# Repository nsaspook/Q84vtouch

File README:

Turbopump RS485 DCU readout emulator

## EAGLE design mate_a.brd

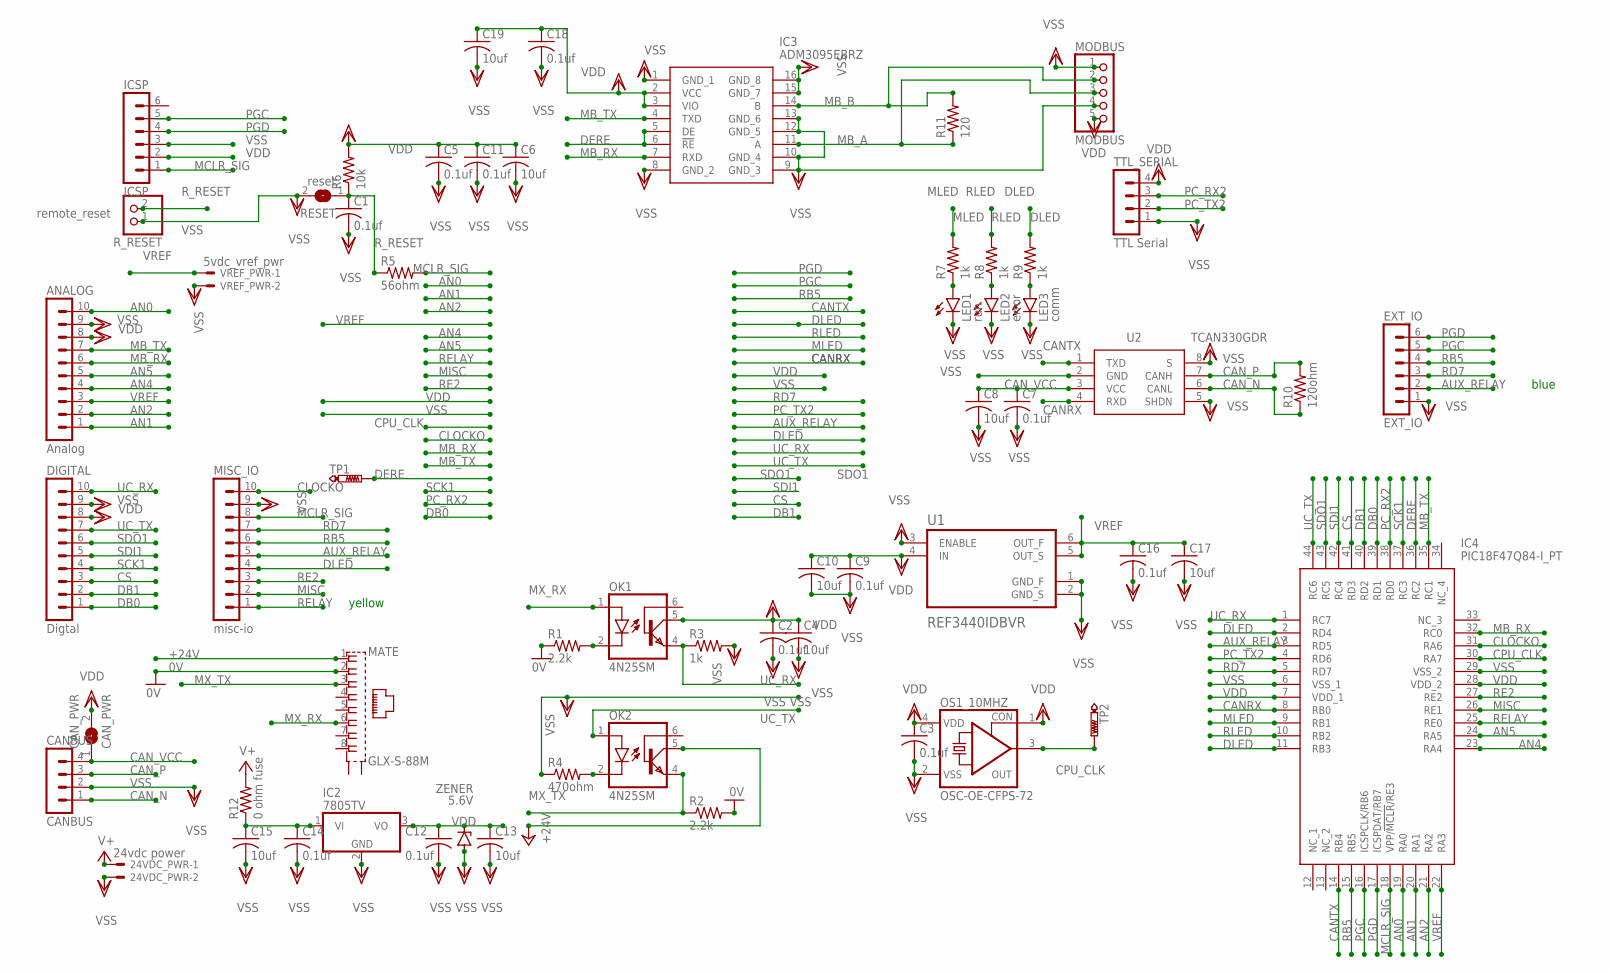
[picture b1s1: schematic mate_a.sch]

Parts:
24VDC_PWR: 24vdc power; 22-23-2021
ANALOG: Analog; MA10-1
C1, C2, C3, C5, C7, C9, C11, C12, C14, C16, C18: 0.1uf; C0805
C4, C6, C8, C10, C13, C15, C17, C19: 10uf; C0805
CANBUS: CANBUS; MA04-1
CAN_PWR: CAN_PWR; SJ
DIGITAL: Digtal; MA10-1
EXT_IO: EXT_IO; MA06-1
IC2: 7805TV; TO220V
IC3: ADM3095EBRZ; SOIC127P600X175-16N
IC4: PIC18F47Q84-I_PT; QFP80P1200X1200X120-44N
ICSP: ICSP; MA06-1
LED1: run; CHIPLED_0805
LED2: error; CHIPLED_0805
LED3: comm; CHIPLED_0805
MATE: GLX-S-88M
MISC_IO: misc-io; MA10-1
MODBUS: MODBUS; 1X05
OK1, OK2: 4N25SM; DIL6-SMD
OS1_10MHZ: OSC-OE-CFPS-72; 7.2X5.2-4-PAD
R1, R2: 2.2k; R0805
R3, R7, R8, R9: 1k; R0805
R4: 470ohm; R0805
R5: 56ohm; R0805
R6: 10k; R0805
R10: 120ohm; R0805
R11: 120; R0805
R12: 0 ohm fuse; R1206
RESET: reset; SJ
R_RESET: remote_reset; 1X02
TP1, TP2: PTR1PAD1-13; P1-13
TTL_SERIAL: TTL Serial; MA04-1
U1: REF3440IDBVR; SOT95P280X145-6N
U2: TCAN330GDR; SOIC127P600X175-8N
VREF_PWR: 5vdc_vref_pwr; 22-23-2021
ZENER: 5.6V; SMB

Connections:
0V: MATE.2, R1.1, R2.2
+24V: MATE.1, OK2.5 (COL)
AN0: ANALOG.10, IC4.19 (RA0)
AN1: ANALOG.1, IC4.20 (RA1)
AN2: ANALOG.2, IC4.21 (RA2)
AN4: ANALOG.4, IC4.23 (RA4)
AN5: ANALOG.5, IC4.24 (RA5)
AUX_RELAY: EXT_IO.2, IC4.3 (RD5), MISC_IO.5
CANRX: IC4.8 (RB0), U2.4 (RXD)
CANTX: IC4.14 (RB4), U2.1 (TXD)
CAN_N: CANBUS.1, R10.1, U2.6 (CANL)
CAN_P: CANBUS.3, R10.2, U2.7 (CANH)
CAN_VCC: C7.1, C8.1, CANBUS.4, CAN_PWR.1, U2.3 (VCC)
CLOCKO: IC4.31 (RA6), MISC_IO.10
CPU_CLK: IC4.30 (RA7), OS1_10MHZ.3 (OUT), TP2.TP
CS: DIGITAL.3, IC4.41 (RD3)
DB0: DIGITAL.1, IC4.39 (RD1)
DB1: DIGITAL.2, IC4.40 (RD2)
DERE: IC3.5 (DE), IC3.6 (!RE), IC4.36 (RC2), TP1.TP
DLED: IC4.2 (RD4), IC4.11 (RB3), MISC_IO.4, R9.2
MB_A: IC3.11 (A), MODBUS.3, R11.1
MB_B: IC3.14 (B), MODBUS.2, R11.2
MB_RX: ANALOG.6, IC3.7 (RXD), IC4.32 (RC0)
MB_TX: ANALOG.7, IC3.4 (TXD), IC4.35 (RC1)
MCLR_SIG: IC4.18 (VPP/!MCLR!/RE3), ICSP.1, MISC_IO.8, R5.2
MISC: IC4.26 (RE1), MISC_IO.2
MLED: IC4.9 (RB1), R7.2
MX_RX: MATE.6, OK1.1 (A)
MX_TX: MATE.3, OK2.4 (EMI), R2.1
unnamed: OK1.2 (C), R1.2
unnamed: C14.1, C15.1, IC2.1 (VI), R12.1
unnamed: OK2.2 (C), R4.2
unnamed: LED1.A, R7.1
unnamed: LED2.A, R8.1
unnamed: LED3.A, R9.1
PC_RX2: IC4.38 (RD0), TTL_SERIAL.3
PC_TX2: IC4.4 (RD6), TTL_SERIAL.2
PGC: EXT_IO.5, IC4.16 (ICSPCLK/RB6), ICSP.5
PGD: EXT_IO.6, IC4.17 (ICSPDAT/RB7), ICSP.4
RB5: EXT_IO.4, IC4.15 (RB5), MISC_IO.6
RD7: EXT_IO.3, IC4.5 (RD7), MISC_IO.7
RE2: IC4.27 (RE2), MISC_IO.3
RELAY: IC4.25 (RE0), MISC_IO.1
RLED: IC4.10 (RB2), R8.2
R_RESET: C1.1, R5.1, R6.1, RESET.1, R_RESET.2
SCK1: DIGITAL.4, IC4.37 (RC3)
SDI1: DIGITAL.5, IC4.42 (RC4)
SDO1: DIGITAL.6, IC4.43 (RC5)
UC_RX: DIGITAL.10, IC4.1 (RC7), OK1.4 (EMI), R3.1
UC_TX: DIGITAL.7, IC4.44 (RC6), OK2.1 (A)
V+: 24VDC_PWR.1, R12.2
VDD: ANALOG.8, C2.1, C3.1, C4.1, C5.1, C6.1, C9.1, C10.1, C11.1, C12.1, C13.1, C18.1, C19.1, CAN_PWR.2, DIGITAL.8, IC2.3 (VO), IC3.2 (VCC), IC3.3 (VIO), IC4.7 (VDD_1), IC4.28 (VDD_2), ICSP.2, MODBUS.5, OK1.5 (COL), OS1_10MHZ.1 (CON), OS1_10MHZ.4 (VDD), R6.2, TTL_SERIAL.4, U1.4 (IN), ZENER.C
VREF: ANALOG.3, C16.1, C17.1, IC4.22 (RA3), U1.5 (OUT_S), U1.6 (OUT_F), VREF_PWR.1
VSS: 24VDC_PWR.2, ANALOG.9, C1.2, C2.2, C3.2, C4.2, C5.2, C6.2, C7.2, C8.2, C9.2, C10.2, C11.2, C12.2, C13.2, C14.2, C15.2, C16.2, C17.2, C18.2, C19.2, CANBUS.2, DIGITAL.9, EXT_IO.1, IC2.2 (GND), IC3.1 (GND_1), IC3.8 (GND_2), IC3.9 (GND_3), IC3.10 (GND_4), IC3.12 (GND_5), IC3.13 (GND_6), IC3.15 (GND_7), IC3.16 (GND_8), IC4.6 (VSS_1), IC4.29 (VSS_2), ICSP.3, LED1.C, LED2.C, LED3.C, MISC_IO.9, MODBUS.1, MODBUS.4, OS1_10MHZ.2 (VSS), R3.2, R4.1, RESET.2, R_RESET.1, TTL_SERIAL.1, U1.1 (GND_F), U1.2 (GND_S), U1.3 (ENABLE), U2.2 (GND), U2.5 (SHDN), U2.8 (S), VREF_PWR.2, ZENER.A

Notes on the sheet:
yellow
blue

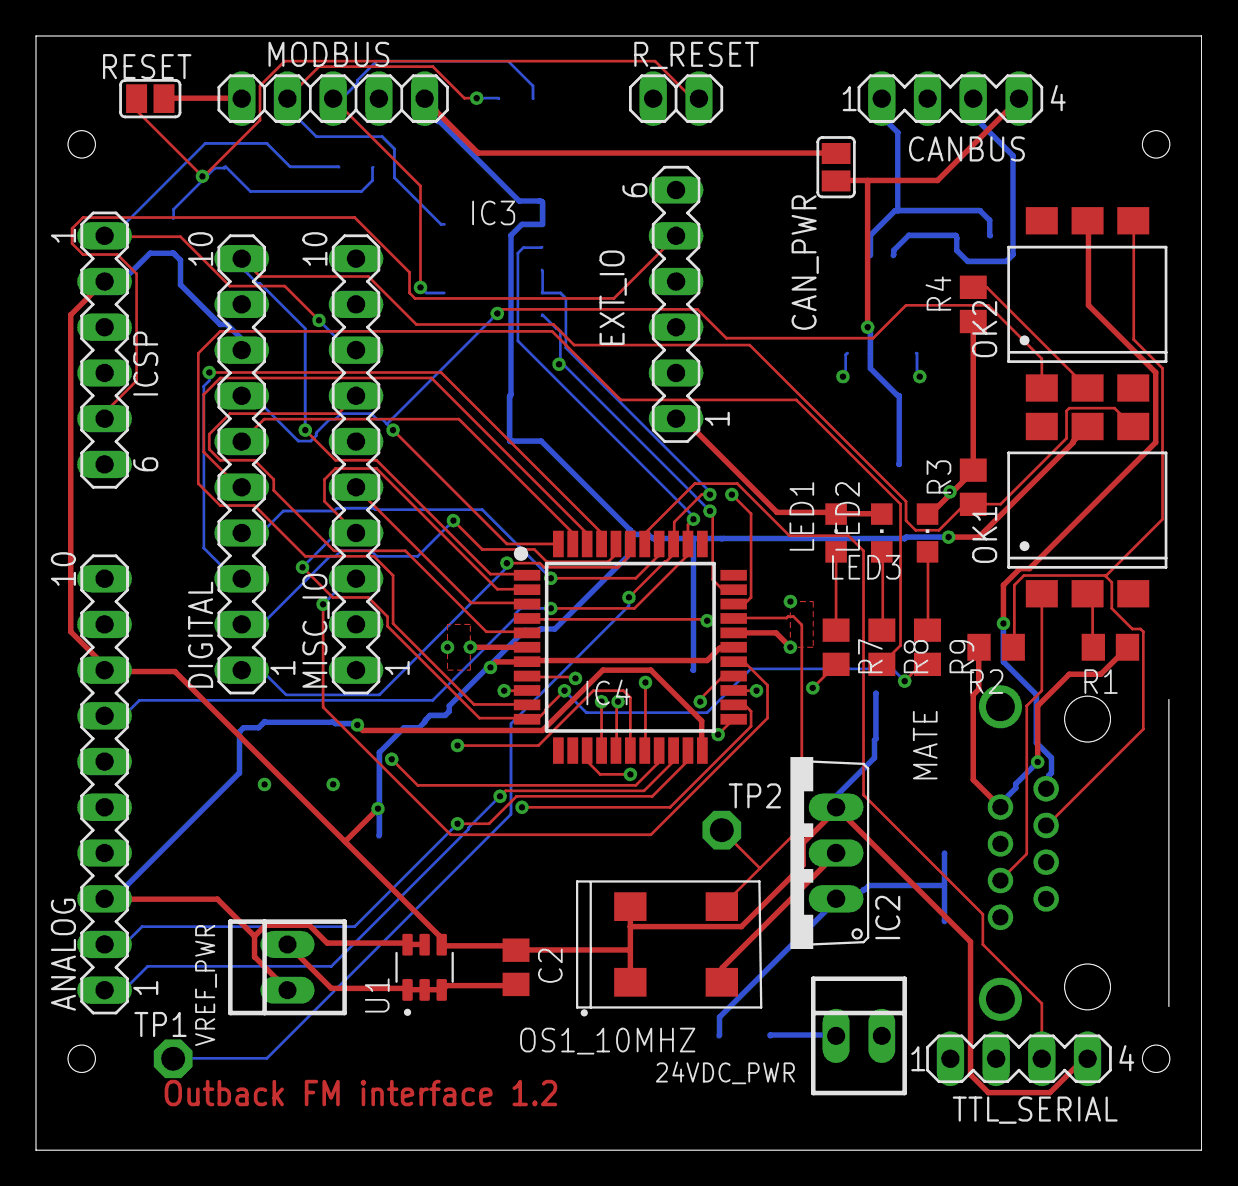
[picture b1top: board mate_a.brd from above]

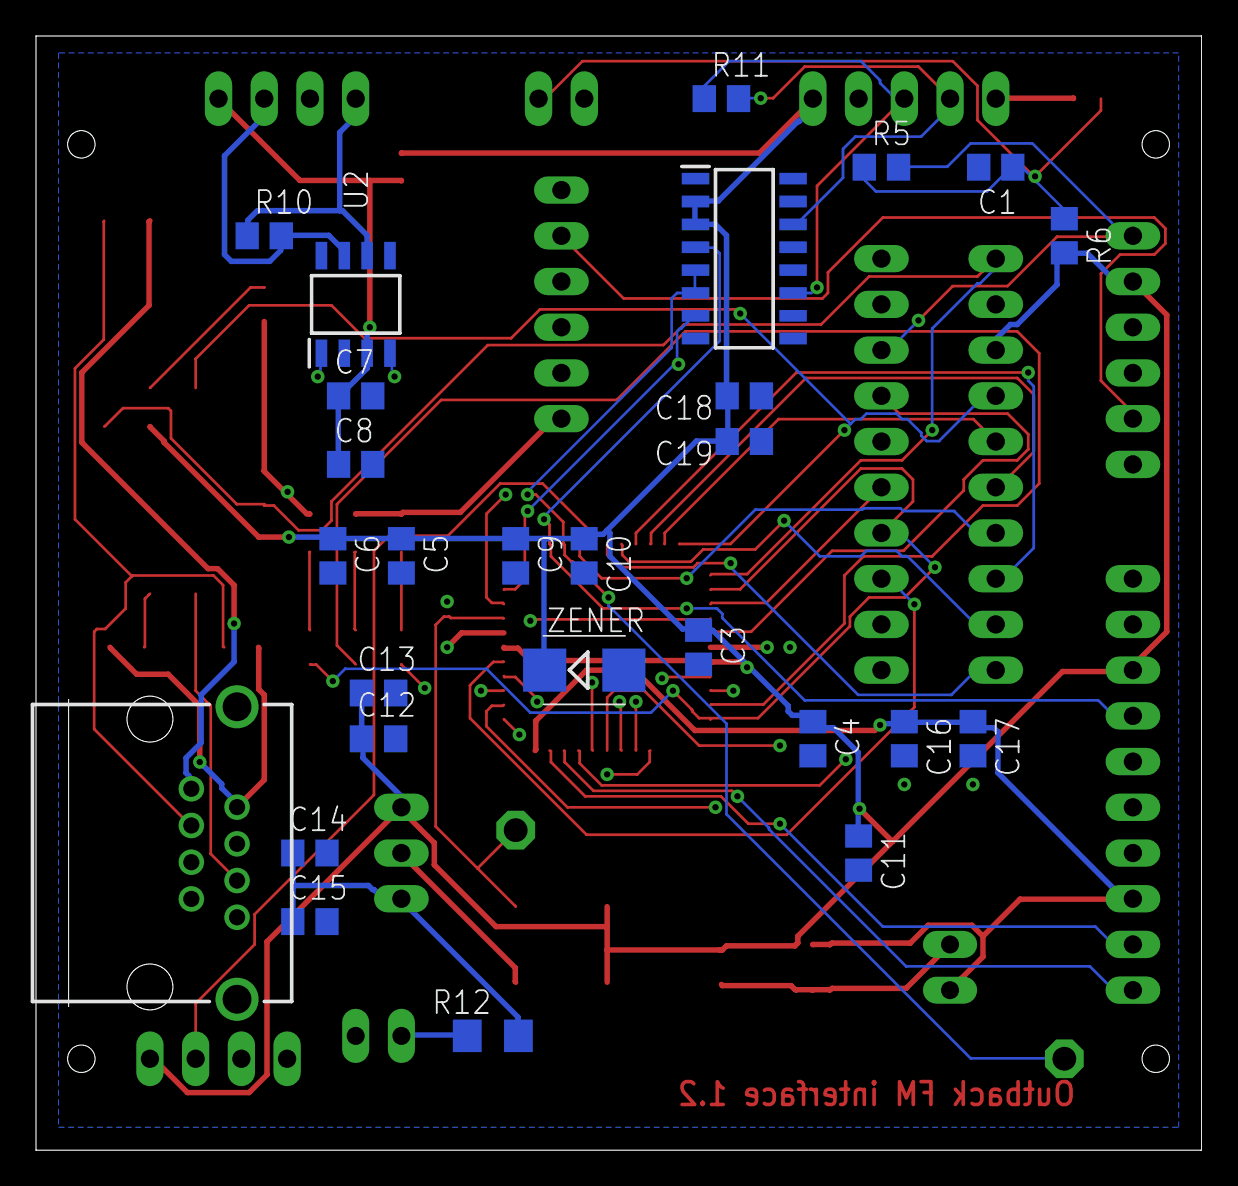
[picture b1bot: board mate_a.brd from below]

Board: 4 copper layers, 64.8 x 61.9 mm, 59 parts (26 on the bottom side), 54 nets.

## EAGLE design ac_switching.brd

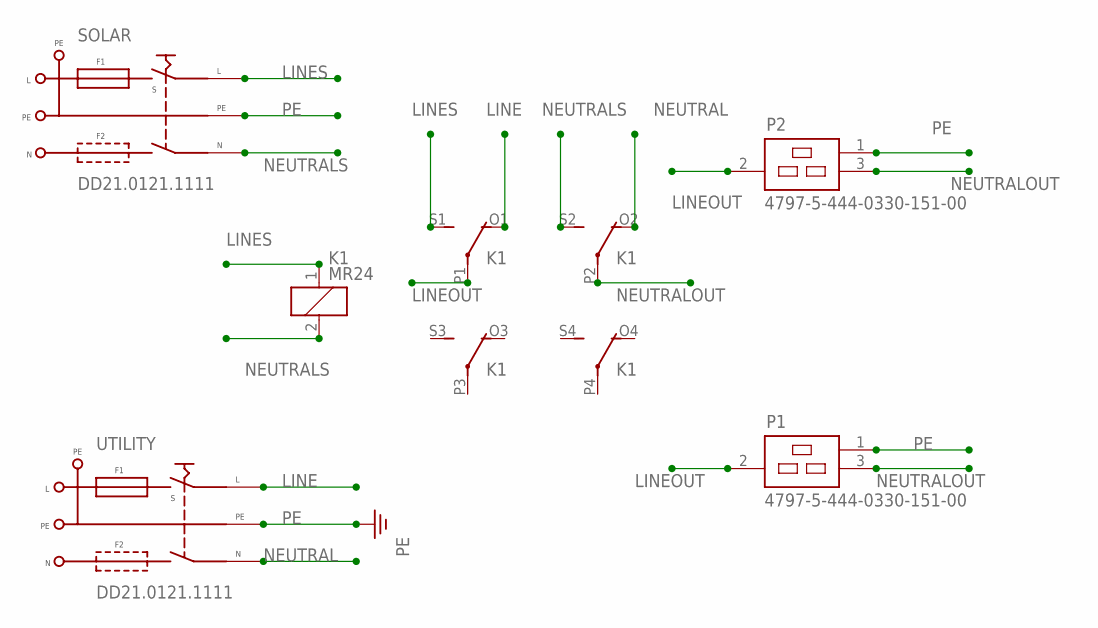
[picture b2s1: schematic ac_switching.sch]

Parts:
K1: MR24
P1, P2: 4797-5-444-0330-151-00; SCHURTER_4797-5-444-0330-151-00
SOLAR: DD21.0121.1111; SCHURTER_DD21.0121.1111
UTILITY: DD21.0121.1111; SCHURTER_DD21.0121.1111

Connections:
LINE: K1.O1 (O), UTILITY.L
LINEOUT: K1.P1, P1.2 (NEUTRAL), P2.2 (NEUTRAL)
LINES: K1.1, K1.S1 (S), SOLAR.L
NEUTRAL: K1.O2 (O), UTILITY.N
NEUTRALOUT: K1.P2, P1.3 (LIVE), P2.3 (LIVE)
NEUTRALS: K1.2, K1.S2 (S), SOLAR.N
PE: P1.1 (GND), P2.1 (GND), SOLAR.PE, UTILITY.PE

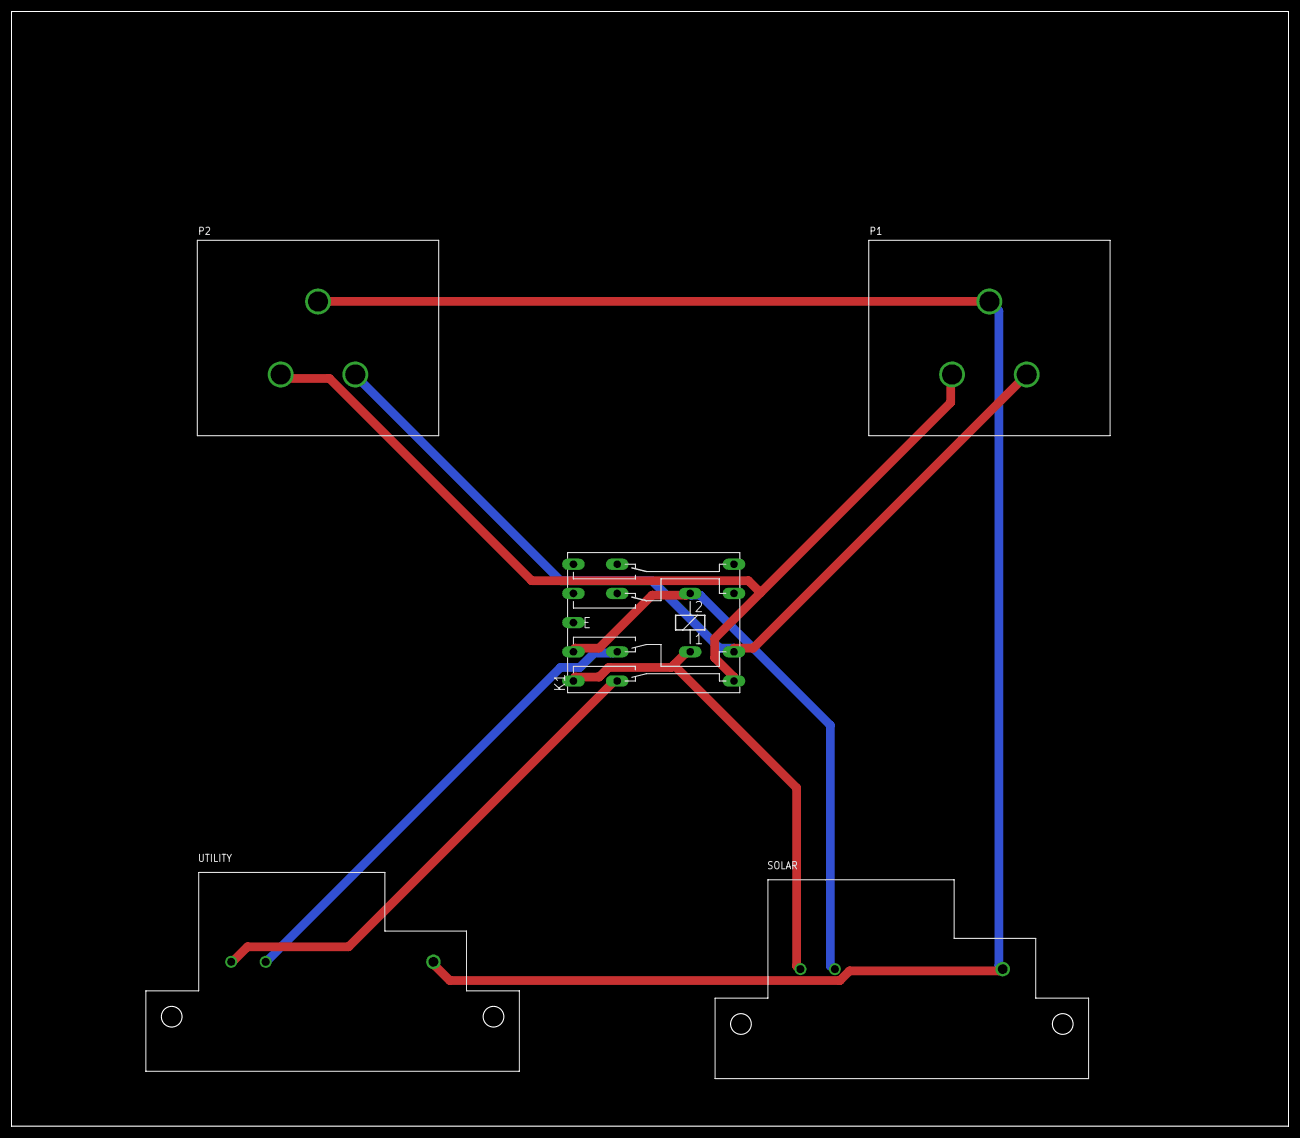
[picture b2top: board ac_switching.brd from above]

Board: 2 copper layers, 222.2 x 194.0 mm, 5 parts (0 on the bottom side), 7 nets.

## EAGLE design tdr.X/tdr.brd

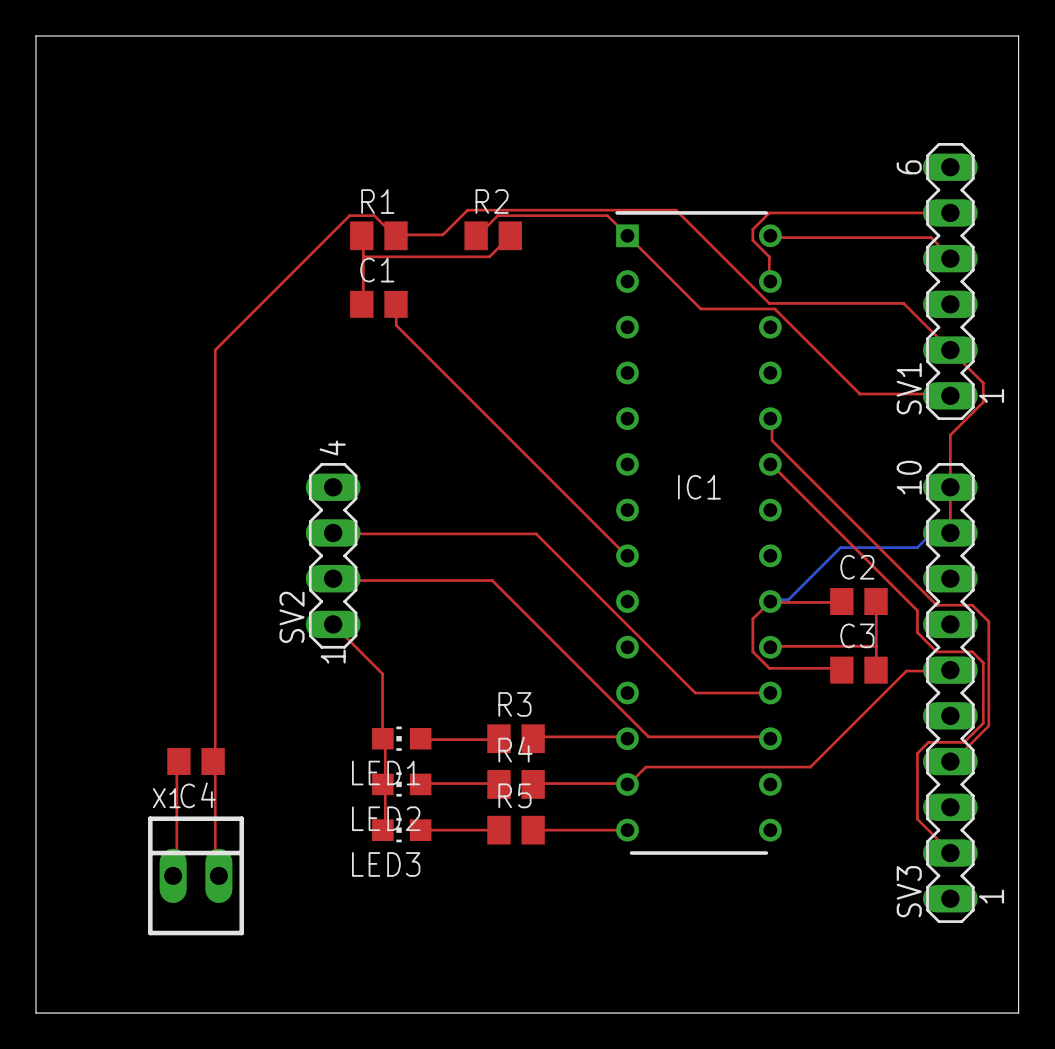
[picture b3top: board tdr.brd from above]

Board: 2 copper layers, 54.6 x 54.3 mm, 17 parts (0 on the bottom side), 16 nets.

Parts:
C1, C2, C4: 0.1uf; C0805
C3: 10uf; C0805
IC1: PIC18F25K22-I_SP; DIP794W56P254L3486H508Q28N
LED1, LED2, LED3: CHIP-LED0805
R1, R2, R3, R4, R5: M0805
SV1: MA06-1
SV2: MA04-1
SV3: MA10-1
X1: 22-23-2021

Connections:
CTED1: IC1.23, SV3.2
CTED2: IC1.24, SV3.4
CTPLS: IC1.13, R4.2, SV3.6
MCLR: IC1.1, R2.1, SV1.1
unnamed: C1.1, R1.1, R2.2
unnamed: IC1.12, R3.2
unnamed: IC1.14, R5.2
unnamed: LED1.A, R3.1
unnamed: LED2.A, R4.1
unnamed: LED3.A, R5.1
PGC: IC1.27, SV1.5
PGD: IC1.28, SV1.4
RX1: IC1.18, SV2.3
TX1: IC1.17, SV2.2
VDD: C2.1, C3.1, C4.1, IC1.20, R1.2, SV1.2, SV3.9, SV3.10, X1.2
VSS: C1.2, C2.2, C3.2, C4.2, IC1.8, IC1.19, LED1.C, LED2.C, LED3.C, SV1.3, SV2.1, SV3.1, SV3.3, SV3.5, X1.1

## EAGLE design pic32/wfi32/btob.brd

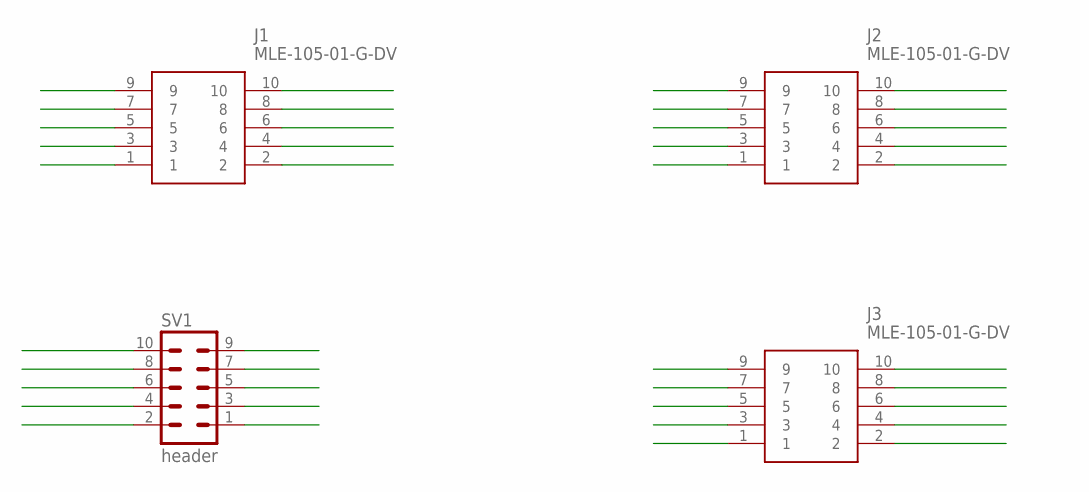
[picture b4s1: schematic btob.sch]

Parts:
J1, J2, J3: MLE-105-01-G-DV
SV1: header; MA05-2

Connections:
unnamed: J1.9, J2.9, J3.9, SV1.9
unnamed: J1.7, J2.7, J3.7, SV1.7
unnamed: J1.5, J2.5, J3.5, SV1.5
unnamed: J1.3, J2.3, J3.3, SV1.3
unnamed: J1.1, J2.1, J3.1, SV1.1
unnamed: J1.10, J2.10, J3.10, SV1.10
unnamed: J1.8, J2.8, J3.8, SV1.8
unnamed: J1.6, J2.6, J3.6, SV1.6
unnamed: J1.4, J2.4, J3.4, SV1.4
unnamed: J1.2, J2.2, J3.2, SV1.2

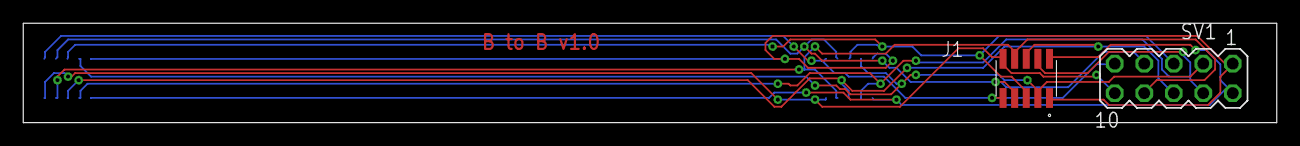
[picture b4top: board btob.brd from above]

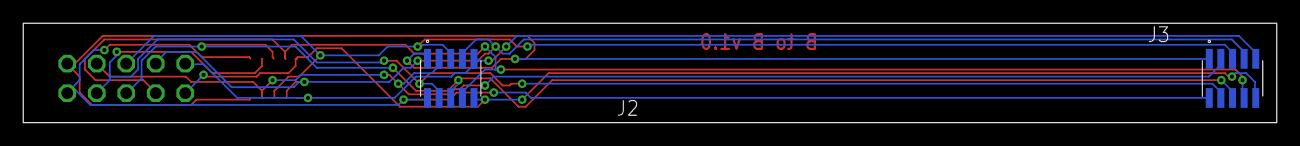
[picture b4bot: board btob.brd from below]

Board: 2 copper layers, 107.9 x 8.6 mm, 4 parts (2 on the bottom side), 10 nets.

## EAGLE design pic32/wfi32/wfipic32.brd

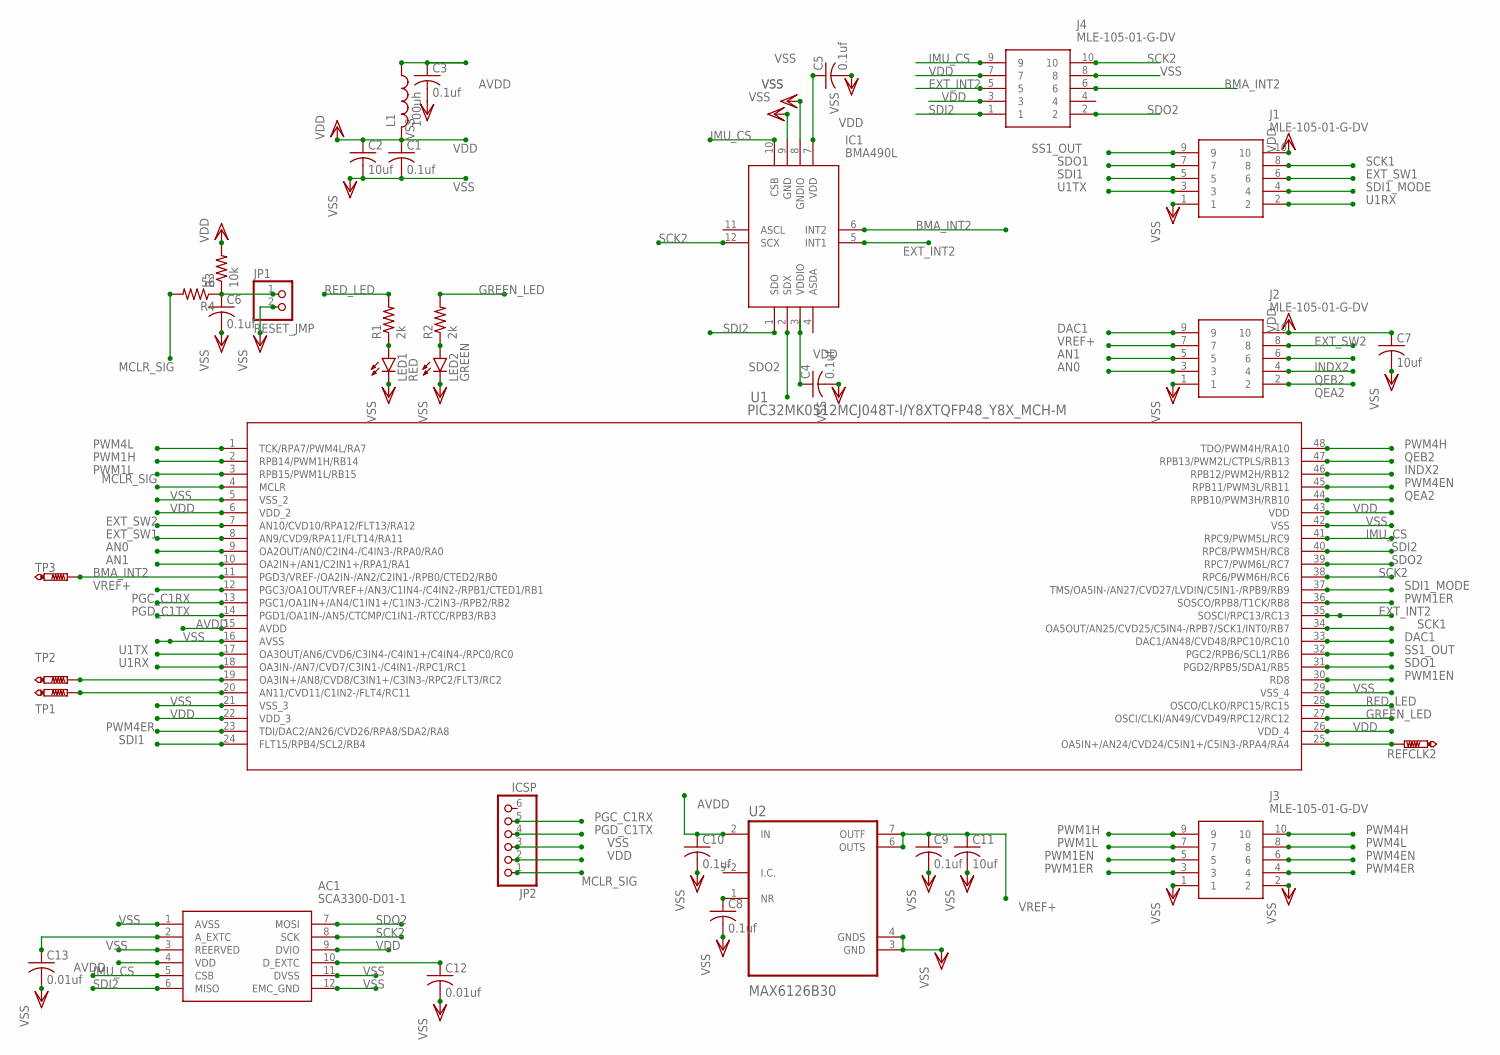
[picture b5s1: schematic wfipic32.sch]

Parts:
AC1: SCA3300-D01-1; SCA3300
C1, C3, C4, C5, C6, C8, C9, C10: 0.1uf; C0805
C2, C7, C11: 10uf; C0805
C12, C13: 0.01uf; C0805
IC1: BMA490L
J1, J2, J3, J4: MLE-105-01-G-DV
JP1: RESET_JMP; 1X02
JP2: ICSP; 1X06
L1: 100uh; L3216C
LED1: RED; CHIPLED_0603
LED2: GREEN; CHIPLED_0603
R1, R2: 2k; M0805
R3: 10k; M0805
R4: 56; M0805
REFCLK2: PTR1PAD1-13; P1-13
TP1, TP2, TP3: PTR1PAD1-13; P1-13
U1: PIC32MK0512MCJ048T-I/Y8XTQFP48_Y8X_MCH-M; TQFP48_Y8X_MCH-M
U2: MAX6126B30; SOP65P490X110-8N

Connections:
AN0: J2.3, U1.9 (OA2OUT/AN0/C2IN4-/C4IN3-/RPA0/RA0)
AN1: J2.5, U1.10 (OA2IN+/AN1/C2IN1+/RPA1/RA1)
AVDD: AC1.4 (VDD), C3.1, C10.1, L1.1, U1.15 (AVDD), U2.2 (IN)
BMA_INT2: IC1.6 (INT2), J4.6, TP3.TP, U1.11 (PGD3/VREF-/OA2IN-/AN2/C2IN1-/RPB0/CTED2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)
DAC1: J2.9, U1.33 (DAC1/AN48/CVD48/RPC10/RC10)
EXT_INT2: IC1.5 (INT1), J4.5, U1.35 (SOSCI/RPC13/RC13)
EXT_SW1: J1.6, U1.8 (AN9/CVD9/RPA11/FLT14/RA11)
EXT_SW2: J2.8, U1.7 (AN10/CVD10/RPA12/FLT13/RA12)
GREEN_LED: R2.2, U1.27 (OSCI/CLKI/AN49/CVD49/RPC12/RC12)
IMU_CS: AC1.5 (CSB), IC1.10 (CSB), J4.9, U1.41 (RPC9/PWM5L/RC9)
INDX2: J2.6, U1.46 (RPB12/PWM2H/RB12)
MCLR_SIG: JP2.1, R4.2, U1.4 (MCLR)
unnamed: LED1.A, R1.1
unnamed: LED2.A, R2.1
unnamed: C6.1, JP1.1, R3.1, R4.1
unnamed: C8.1, U2.1 (NR)
unnamed: TP1.TP, U1.20 (AN11/CVD11/C1IN2-/FLT4/RC11)
unnamed: TP2.TP, U1.19 (OA3IN+/AN8/CVD8/C3IN1+/C3IN3-/RPC2/FLT3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)
unnamed: AC1.10 (D_EXTC), C12.1
unnamed: REFCLK2.TP, U1.25 (OA5IN+/AN24/CVD24/C5IN1+/C5IN3-/RPA4/RA4)
unnamed: AC1.2 (A_EXTC), C13.1
PGC_C1RX: JP2.5, U1.13 (PGC1/OA1IN+/AN4/C1IN1+/C1IN3-/C2IN3-/RP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)
PGD_C1TX: JP2.4, U1.14 (PGD1/OA1IN-/AN5/CTCMP/C1IN1-/RTCC/RPB3/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)
PWM1EN: J3.5, U1.30 (RD8)
PWM1ER: J3.3, U1.36 (SOSCO/RPB8/T1CK/RB8)
PWM1H: J3.9, U1.2 (RPB14/PWM1H/RB14)
PWM1L: J3.7, U1.3 (RPB15/PWM1L/RB15)
PWM4EN: J3.6, U1.45 (RPB11/PWM3L/RB11)
PWM4ER: J3.4, U1.23 (TDI/DAC2/AN26/CVD26/RPA8/SDA2/RA8)
PWM4H: J3.10, U1.48 (TDO/PWM4H/RA10)
PWM4L: J3.8, U1.1 (TCK/RPA7/PWM4L/RA7)
QEA2: J2.2, U1.44 (RPB10/PWM3H/RB10)
QEB2: J2.4, U1.47 (RPB13/PWM2L/CTPLS/RB13)
RED_LED: R1.2, U1.28 (OSCO/CLKO/RPC15/RC15)
SCK1: J1.8, U1.34 (OA5OUT/AN25/CVD25/C5IN4-/RPB7/SCK1/INT0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)
SCK2: AC1.8 (SCK), IC1.12 (SCX), J4.10, U1.38 (RPC6/PWM6H/RC6)
SDI1: J1.5, U1.24 (FLT15/RPB4/SCL2/RB4)
SDI1_MODE: J1.4, U1.37 (TMS/OA5IN-/AN27/CVD27/LVDIN/C5IN1-/RPB9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)
SDI2: AC1.6 (MISO), IC1.1 (SDO), J4.1, U1.40 (RPC8/PWM5H/RC8)
SDO1: J1.7, U1.31 (PGD2/RPB5/SDA1/RB5)
SDO2: AC1.7 (MOSI), IC1.2 (SDX), J4.2, U1.39 (RPC7/PWM6L/RC7)
SS1_OUT: J1.9, U1.32 (PGC2/RPB6/SCL1/RB6)
U1RX: J1.2, U1.18 (OA3IN-/AN7/CVD7/C3IN1-/C4IN1-/RPC1/RC1)
U1TX: J1.3, U1.17 (OA3OUT/AN6/CVD6/C3IN4-/C4IN1+/C4IN4-/RP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)
VDD: AC1.9 (DVIO), C1.1, C2.1, C4.1, C5.1, C7.1, IC1.3 (VDDIO), IC1.7 (VDD), J1.10, J2.10, J4.3, J4.7, JP2.2, L1.2, R3.2, U1.6 (VDD_2), U1.22 (VDD_3), U1.26 (VDD_4), U1.43 (VDD)
VREF+: C9.1, C11.1, J2.7, U1.12 (PGC3/OA1OUT/VREF+/AN3/C1IN4-/C4IN2-/RPB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), U2.6 (OUTS), U2.7 (OUTF)
VSS: AC1.1 (AVSS), AC1.3 (REERVED), AC1.11 (DVSS), AC1.12 (EMC_GND), C1.2, C2.2, C3.2, C4.2, C5.2, C6.2, C7.2, C8.2, C9.2, C10.2, C11.2, C12.2, C13.2, IC1.8 (GNDIO), IC1.9 (GND), J1.1, J2.1, J3.1, J3.2, J4.8, JP1.2, JP2.3, LED1.C, LED2.C, U1.5 (VSS_2), U1.16 (AVSS), U1.21 (VSS_3), U1.29 (VSS_4), U1.42 (VSS), U2.3 (GND), U2.4 (GNDS)

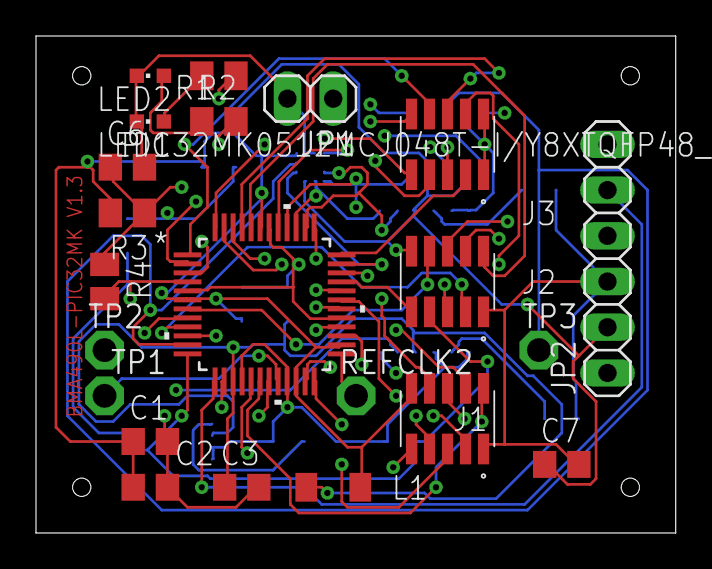
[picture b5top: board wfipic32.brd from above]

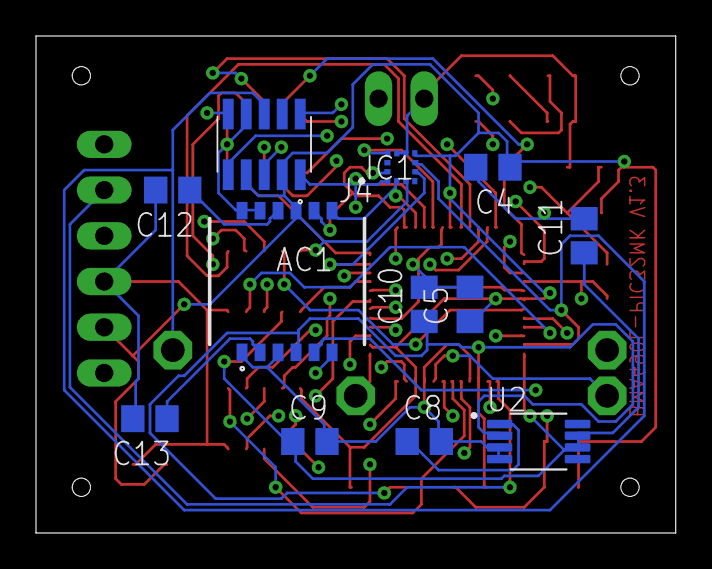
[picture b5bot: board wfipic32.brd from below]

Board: 4 copper layers, 35.5 x 27.6 mm, 34 parts (12 on the bottom side), 47 nets.

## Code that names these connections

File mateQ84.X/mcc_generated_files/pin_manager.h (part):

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// get/set channel_ANA0 aliases
#define channel_ANA0_TRIS                 TRISAbits.TRISA0
#define channel_ANA0_LAT                  LATAbits.LATA0
#define channel_ANA0_PORT                 PORTAbits.RA0
#define channel_ANA0_WPU                  WPUAbits.WPUA0
#define channel_ANA0_OD                   ODCONAbits.ODCA0
#define channel_ANA0_ANS                  ANSELAbits.ANSELA0
#define channel_ANA0_SetHigh()            do { LATAbits.LATA0 = 1; } while(0)
#define channel_ANA0_SetLow()             do { LATAbits.LATA0 = 0; } while(0)
#define channel_ANA0_Toggle()             do { LATAbits.LATA0 = ~LATAbits.LATA0; } while(0)
#define channel_ANA0_GetValue()           PORTAbits.RA0
#define channel_ANA0_SetDigitalInput()    do { TRISAbits.TRISA0 = 1; } while(0)
#define channel_ANA0_SetDigitalOutput()   do { TRISAbits.TRISA0 = 0; } while(0)
#define channel_ANA0_SetPullup()          do { WPUAbits.WPUA0 = 1; } while(0)
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// get/set M_SWITCH aliases
#define M_SWITCH_TRIS                 TRISAbits.TRISA1
#define M_SWITCH_LAT                  LATAbits.LATA1
#define M_SWITCH_PORT                 PORTAbits.RA1
#define M_SWITCH_WPU                  WPUAbits.WPUA1
#define M_SWITCH_OD                   ODCONAbits.ODCA1
#define M_SWITCH_ANS                  ANSELAbits.ANSELA1
#define M_SWITCH_SetHigh()            do { LATAbits.LATA1 = 1; } while(0)
#define M_SWITCH_SetLow()             do { LATAbits.LATA1 = 0; } while(0)
#define M_SWITCH_Toggle()             do { LATAbits.LATA1 = ~LATAbits.LATA1; } while(0)
#define M_SWITCH_GetValue()           PORTAbits.RA1
#define M_SWITCH_SetDigitalInput()    do { TRISAbits.TRISA1 = 1; } while(0)
#define M_SWITCH_SetDigitalOutput()   do { TRISAbits.TRISA1 = 0; } while(0)
#define M_SWITCH_SetPullup()          do { WPUAbits.WPUA1 = 1; } while(0)
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// get/set L_SWITCH aliases
#define L_SWITCH_TRIS                 TRISAbits.TRISA2
#define L_SWITCH_LAT                  LATAbits.LATA2
#define L_SWITCH_PORT                 PORTAbits.RA2
#define L_SWITCH_WPU                  WPUAbits.WPUA2
#define L_SWITCH_OD                   ODCONAbits.ODCA2
#define L_SWITCH_ANS                  ANSELAbits.ANSELA2
#define L_SWITCH_SetHigh()            do { LATAbits.LATA2 = 1; } while(0)
#define L_SWITCH_SetLow()             do { LATAbits.LATA2 = 0; } while(0)
#define L_SWITCH_Toggle()             do { LATAbits.LATA2 = ~LATAbits.LATA2; } while(0)
#define L_SWITCH_GetValue()           PORTAbits.RA2
#define L_SWITCH_SetDigitalInput()    do { TRISAbits.TRISA2 = 1; } while(0)
#define L_SWITCH_SetDigitalOutput()   do { TRISAbits.TRISA2 = 0; } while(0)
#define L_SWITCH_SetPullup()          do { WPUAbits.WPUA2 = 1; } while(0)
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#define RA3_SetHigh()            do { LATAbits.LATA3 = 1; } while(0)
#define RA3_SetLow()             do { LATAbits.LATA3 = 0; } while(0)
#define RA3_Toggle()             do { LATAbits.LATA3 = ~LATAbits.LATA3; } while(0)
#define RA3_GetValue()              PORTAbits.RA3
#define RA3_SetDigitalInput()    do { TRISAbits.TRISA3 = 1; } while(0)
#define RA3_SetDigitalOutput()   do { TRISAbits.TRISA3 = 0; } while(0)
#define RA3_SetPullup()             do { WPUAbits.WPUA3 = 1; } while(0)
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// get/set channel_ANA4 aliases
#define channel_ANA4_TRIS                 TRISAbits.TRISA4
#define channel_ANA4_LAT                  LATAbits.LATA4
#define channel_ANA4_PORT                 PORTAbits.RA4
#define channel_ANA4_WPU                  WPUAbits.WPUA4
#define channel_ANA4_OD                   ODCONAbits.ODCA4
#define channel_ANA4_ANS                  ANSELAbits.ANSELA4
#define channel_ANA4_SetHigh()            do { LATAbits.LATA4 = 1; } while(0)
#define channel_ANA4_SetLow()             do { LATAbits.LATA4 = 0; } while(0)
#define channel_ANA4_Toggle()             do { LATAbits.LATA4 = ~LATAbits.LATA4; } while(0)
#define channel_ANA4_GetValue()           PORTAbits.RA4
#define channel_ANA4_SetDigitalInput()    do { TRISAbits.TRISA4 = 1; } while(0)
#define channel_ANA4_SetDigitalOutput()   do { TRISAbits.TRISA4 = 0; } while(0)
#define channel_ANA4_SetPullup()          do { WPUAbits.WPUA4 = 1; } while(0)
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// get/set A_SWITCH aliases
#define A_SWITCH_TRIS                 TRISAbits.TRISA5
#define A_SWITCH_LAT                  LATAbits.LATA5
#define A_SWITCH_PORT                 PORTAbits.RA5
#define A_SWITCH_WPU                  WPUAbits.WPUA5
#define A_SWITCH_OD                   ODCONAbits.ODCA5
#define A_SWITCH_ANS                  ANSELAbits.ANSELA5
#define A_SWITCH_SetHigh()            do { LATAbits.LATA5 = 1; } while(0)
#define A_SWITCH_SetLow()             do { LATAbits.LATA5 = 0; } while(0)
#define A_SWITCH_Toggle()             do { LATAbits.LATA5 = ~LATAbits.LATA5; } while(0)
#define A_SWITCH_GetValue()           PORTAbits.RA5
#define A_SWITCH_SetDigitalInput()    do { TRISAbits.TRISA5 = 1; } while(0)
#define A_SWITCH_SetDigitalOutput()   do { TRISAbits.TRISA5 = 0; } while(0)
#define A_SWITCH_SetPullup()          do { WPUAbits.WPUA5 = 1; } while(0)
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#define RB0_SetHigh()            do { LATBbits.LATB0 = 1; } while(0)
#define RB0_SetLow()             do { LATBbits.LATB0 = 0; } while(0)
#define RB0_Toggle()             do { LATBbits.LATB0 = ~LATBbits.LATB0; } while(0)
#define RB0_GetValue()              PORTBbits.RB0
#define RB0_SetDigitalInput()    do { TRISBbits.TRISB0 = 1; } while(0)
#define RB0_SetDigitalOutput()   do { TRISBbits.TRISB0 = 0; } while(0)
#define RB0_SetPullup()             do { WPUBbits.WPUB0 = 1; } while(0)
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// get/set MLED aliases
#define MLED_TRIS                 TRISBbits.TRISB1
#define MLED_LAT                  LATBbits.LATB1
#define MLED_PORT                 PORTBbits.RB1
#define MLED_WPU                  WPUBbits.WPUB1
#define MLED_OD                   ODCONBbits.ODCB1
#define MLED_ANS                  ANSELBbits.ANSELB1
#define MLED_SetHigh()            do { LATBbits.LATB1 = 1; } while(0)
#define MLED_SetLow()             do { LATBbits.LATB1 = 0; } while(0)
#define MLED_Toggle()             do { LATBbits.LATB1 = ~LATBbits.LATB1; } while(0)
#define MLED_GetValue()           PORTBbits.RB1
#define MLED_SetDigitalInput()    do { TRISBbits.TRISB1 = 1; } while(0)
#define MLED_SetDigitalOutput()   do { TRISBbits.TRISB1 = 0; } while(0)
#define MLED_SetPullup()          do { WPUBbits.WPUB1 = 1; } while(0)
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// get/set RLED aliases
#define RLED_TRIS                 TRISBbits.TRISB2
#define RLED_LAT                  LATBbits.LATB2
#define RLED_PORT                 PORTBbits.RB2
#define RLED_WPU                  WPUBbits.WPUB2
#define RLED_OD                   ODCONBbits.ODCB2
#define RLED_ANS                  ANSELBbits.ANSELB2
#define RLED_SetHigh()            do { LATBbits.LATB2 = 1; } while(0)
#define RLED_SetLow()             do { LATBbits.LATB2 = 0; } while(0)
#define RLED_Toggle()             do { LATBbits.LATB2 = ~LATBbits.LATB2; } while(0)
#define RLED_GetValue()           PORTBbits.RB2
#define RLED_SetDigitalInput()    do { TRISBbits.TRISB2 = 1; } while(0)
#define RLED_SetDigitalOutput()   do { TRISBbits.TRISB2 = 0; } while(0)
#define RLED_SetPullup()          do { WPUBbits.WPUB2 = 1; } while(0)
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// get/set DLED1 aliases
#define DLED1_TRIS                 TRISBbits.TRISB3
#define DLED1_LAT                  LATBbits.LATB3
#define DLED1_PORT                 PORTBbits.RB3
#define DLED1_WPU                  WPUBbits.WPUB3
#define DLED1_OD                   ODCONBbits.ODCB3
#define DLED1_ANS                  ANSELBbits.ANSELB3
#define DLED1_SetHigh()            do { LATBbits.LATB3 = 1; } while(0)
#define DLED1_SetLow()             do { LATBbits.LATB3 = 0; } while(0)
#define DLED1_Toggle()             do { LATBbits.LATB3 = ~LATBbits.LATB3; } while(0)
#define DLED1_GetValue()           PORTBbits.RB3
#define DLED1_SetDigitalInput()    do { TRISBbits.TRISB3 = 1; } while(0)
#define DLED1_SetDigitalOutput()   do { TRISBbits.TRISB3 = 0; } while(0)
#define DLED1_SetPullup()          do { WPUBbits.WPUB3 = 1; } while(0)
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#define RB4_SetHigh()            do { LATBbits.LATB4 = 1; } while(0)
#define RB4_SetLow()             do { LATBbits.LATB4 = 0; } while(0)
#define RB4_Toggle()             do { LATBbits.LATB4 = ~LATBbits.LATB4; } while(0)
#define RB4_GetValue()              PORTBbits.RB4
#define RB4_SetDigitalInput()    do { TRISBbits.TRISB4 = 1; } while(0)
#define RB4_SetDigitalOutput()   do { TRISBbits.TRISB4 = 0; } while(0)
#define RB4_SetPullup()             do { WPUBbits.WPUB4 = 1; } while(0)
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// get/set IO_RB5 aliases
#define IO_RB5_TRIS                 TRISBbits.TRISB5
#define IO_RB5_LAT                  LATBbits.LATB5
#define IO_RB5_PORT                 PORTBbits.RB5
#define IO_RB5_WPU                  WPUBbits.WPUB5
#define IO_RB5_OD                   ODCONBbits.ODCB5
#define IO_RB5_ANS                  ANSELBbits.ANSELB5
#define IO_RB5_SetHigh()            do { LATBbits.LATB5 = 1; } while(0)
#define IO_RB5_SetLow()             do { LATBbits.LATB5 = 0; } while(0)
#define IO_RB5_Toggle()             do { LATBbits.LATB5 = ~LATBbits.LATB5; } while(0)
#define IO_RB5_GetValue()           PORTBbits.RB5
#define IO_RB5_SetDigitalInput()    do { TRISBbits.TRISB5 = 1; } while(0)
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
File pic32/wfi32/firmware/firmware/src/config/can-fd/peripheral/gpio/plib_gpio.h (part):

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// *****************************************************************************


/*** Macros for EXT_SW2 pin ***/
#define EXT_SW2_Set()               (LATASET = (1U<<12))
#define EXT_SW2_Clear()             (LATACLR = (1U<<12))
#define EXT_SW2_Toggle()            (LATAINV= (1U<<12))
#define EXT_SW2_OutputEnable()      (TRISACLR = (1U<<12))
#define EXT_SW2_InputEnable()       (TRISASET = (1U<<12))
#define EXT_SW2_Get()               ((PORTA >> 12) & 0x1U)
#define EXT_SW2_PIN                  GPIO_PIN_RA12

/*** Macros for EXT_SW1 pin ***/
#define EXT_SW1_Set()               (LATASET = (1U<<11))
#define EXT_SW1_Clear()             (LATACLR = (1U<<11))
#define EXT_SW1_Toggle()            (LATAINV= (1U<<11))
#define EXT_SW1_OutputEnable()      (TRISACLR = (1U<<11))
#define EXT_SW1_InputEnable()       (TRISASET = (1U<<11))
#define EXT_SW1_Get()               ((PORTA >> 11) & 0x1U)
#define EXT_SW1_PIN                  GPIO_PIN_RA11

/*** Macros for TP3 pin ***/
#define TP3_Set()               (LATBSET = (1U<<0))
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#define TP1_Get()               ((PORTC >> 11) & 0x1U)
#define TP1_PIN                  GPIO_PIN_RC11

/*** Macros for PWM4ER pin ***/
#define PWM4ER_Set()               (LATASET = (1U<<8))
#define PWM4ER_Clear()             (LATACLR = (1U<<8))
#define PWM4ER_Toggle()            (LATAINV= (1U<<8))
#define PWM4ER_OutputEnable()      (TRISACLR = (1U<<8))
#define PWM4ER_InputEnable()       (TRISASET = (1U<<8))
#define PWM4ER_Get()               ((PORTA >> 8) & 0x1U)
#define PWM4ER_PIN                  GPIO_PIN_RA8

/*** Macros for REFCLK2 pin ***/
#define REFCLK2_Get()               ((PORTA >> 4) & 0x1U)
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#define LED_RED_Get()               ((PORTC >> 15) & 0x1U)
#define LED_RED_PIN                  GPIO_PIN_RC15

/*** Macros for PWM1EN pin ***/
#define PWM1EN_Set()               (LATDSET = (1U<<8))
#define PWM1EN_Clear()             (LATDCLR = (1U<<8))
#define PWM1EN_Toggle()            (LATDINV= (1U<<8))
#define PWM1EN_OutputEnable()      (TRISDCLR = (1U<<8))
#define PWM1EN_InputEnable()       (TRISDSET = (1U<<8))
#define PWM1EN_Get()               ((PORTD >> 8) & 0x1U)
#define PWM1EN_PIN                  GPIO_PIN_RD8

/*** Macros for DIS_CS pin ***/
#define DIS_CS_Set()               (LATBSET = (1U<<6))
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#define DIS_CS_Get()               ((PORTB >> 6) & 0x1U)
#define DIS_CS_PIN                  GPIO_PIN_RB6

/*** Macros for PWM1ER pin ***/
#define PWM1ER_Set()               (LATBSET = (1U<<8))
#define PWM1ER_Clear()             (LATBCLR = (1U<<8))
#define PWM1ER_Toggle()            (LATBINV= (1U<<8))
#define PWM1ER_OutputEnable()      (TRISBCLR = (1U<<8))
#define PWM1ER_InputEnable()       (TRISBSET = (1U<<8))
#define PWM1ER_Get()               ((PORTB >> 8) & 0x1U)
#define PWM1ER_PIN                  GPIO_PIN_RB8

/*** Macros for DIS_MODE pin ***/
#define DIS_MODE_Set()               (LATBSET = (1U<<9))
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#define DIS_MODE_Get()               ((PORTB >> 9) & 0x1U)
#define DIS_MODE_PIN                  GPIO_PIN_RB9

/*** Macros for IMU_CS pin ***/
#define IMU_CS_Set()               (LATCSET = (1U<<9))
#define IMU_CS_Clear()             (LATCCLR = (1U<<9))
#define IMU_CS_Toggle()            (LATCINV= (1U<<9))
#define IMU_CS_OutputEnable()      (TRISCCLR = (1U<<9))
#define IMU_CS_InputEnable()       (TRISCSET = (1U<<9))
#define IMU_CS_Get()               ((PORTC >> 9) & 0x1U)
#define IMU_CS_PIN                  GPIO_PIN_RC9

/*** Macros for PWM4EN pin ***/
#define PWM4EN_Set()               (LATBSET = (1U<<11))
#define PWM4EN_Clear()             (LATBCLR = (1U<<11))
#define PWM4EN_Toggle()            (LATBINV= (1U<<11))
#define PWM4EN_OutputEnable()      (TRISBCLR = (1U<<11))
#define PWM4EN_InputEnable()       (TRISBSET = (1U<<11))
#define PWM4EN_Get()               ((PORTB >> 11) & 0x1U)
#define PWM4EN_PIN                  GPIO_PIN_RB11


// *****************************************************************************
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
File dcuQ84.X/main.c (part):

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#pragma config FCMENS = ON      // Fail-Safe Clock Monitor -Secondary XTAL Enable bit (FSCM timer will set FSCMS bit and OSFIF interrupt on Secondary XTAL failure)

// CONFIG3
#pragma config MCLRE = EXTMCLR  // MCLR Enable bit (If LVP = 0, MCLR pin is MCLR; If LVP = 1, RE3 pin function is MCLR )
#pragma config PWRTS = PWRT_OFF // Power-up timer selection bits (PWRT is disabled)
#pragma config MVECEN = ON      // Multi-vector enable bit (Multi-vector enabled, Vector table used for interrupts)
#pragma config IVT1WAY = ON     // IVTLOCK bit One-way set enable bit (IVTLOCKED bit can be cleared and set only once)
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#pragma config WRTAPP = OFF     // Application Block write protection bit (Application Block not write protected)

// CONFIG9
#pragma config BOOTPINSEL = RC5 // CRC on boot output pin selection (CRC on boot output pin is RC5)
#pragma config BPEN = OFF       // CRC on boot output pin enable bit (CRC on boot output pin disabled)
#pragma config ODCON = OFF      // CRC on boot output pin open drain bit (Pin drives both high-going and low-going signals)

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	volt_whole = voltage / 100;
}

/* Misc ACSII spinner character generator, stores position for each shape */
char spinners(uint8_t shape, const uint8_t reset)
{
	static uint8_t s[MAX_SHAPES];
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
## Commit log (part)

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2023-06-20 up up#
2023-09-27 :wq up
2023-11-11 change can filter method to maybe allow for node ID from the CPU ID
2023-12-22 version 1.0 production release
2024-01-01 iup[
2024-02-02 Three canbus packet logging updates
2024-06-10 dimming updates to master
2024-06-18 float fixes
2024-06-19 convert to syslog for perror
2024-06-27 up:wq
2024-10-12 v2.01
2024-11-17 up:wq `:wq
2024-12-03 case files
2024-12-16 new rj45
2024-12-16 1.3 board
2024-12-31 change pcb name
2025-01-30 up V2.03
2025-02-16 rename to ha_canfd
2025-05-22 minor FM comm fixes and lib updates
2025-08-09 change ipaddress
2025-08-17 up docs up# new file: html/adc_8c.html
2025-09-02 up restart fixes
2025-09-04 up restart code

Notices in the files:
mateQ84.X/mcc_generated_files/pin_manager.h:
(c) 2018 Microchip Technology Inc. and its subsidiaries.
pic32/wfi32/firmware/firmware/src/config/can-fd/peripheral/gpio/plib_gpio.h:
Copyright (C) 2019 Microchip Technology Inc. and its subsidiaries.
parts and their libraries:
COPYRIGHT: Copyright (C) 2022 Ultra Librarian. All rights reserved.
